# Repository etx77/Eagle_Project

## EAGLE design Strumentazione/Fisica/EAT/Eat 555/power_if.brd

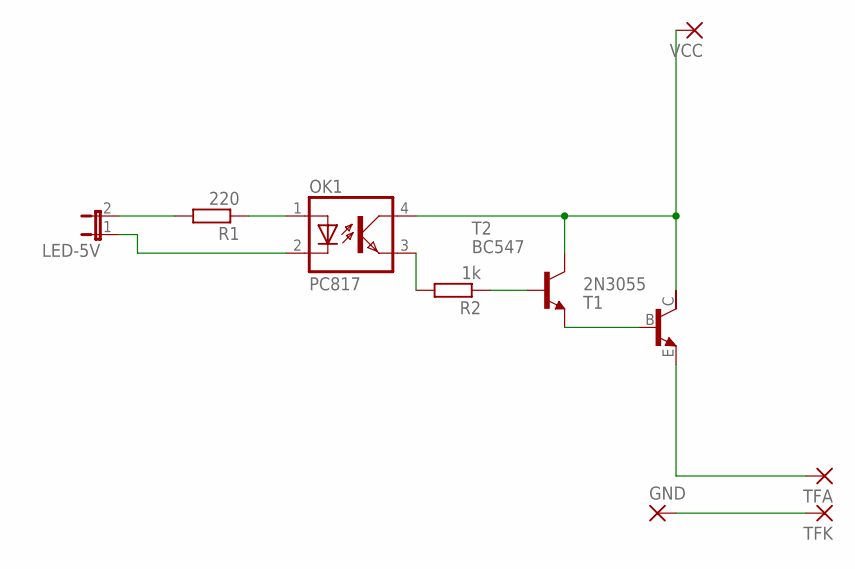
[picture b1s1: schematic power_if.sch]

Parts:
GND: 3,81/1,4
LED-5V: JP1E; JP1
OK1: PC817; DIL04
R1: 220; 0207/10
R2: 1k; 0207/10
T1: 2N3055; TO3
T2: BC547; TO92
TFA: 3,81/1,4
TFK: 3,81/1,4
VCC: 3,81/1,4

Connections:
unnamed: OK1.4 (COL), T1.C, T2.3 (C), VCC.1
unnamed: T1.B, T2.1 (E)
unnamed: OK1.3 (EMIT), R2.2
unnamed: R2.1, T2.2 (B)
unnamed: OK1.1 (A), R1.1
unnamed: LED-5V.2, R1.2
unnamed: LED-5V.1, OK1.2 (C)
unnamed: T1.E, TFA.1
unnamed: GND.1, TFK.1

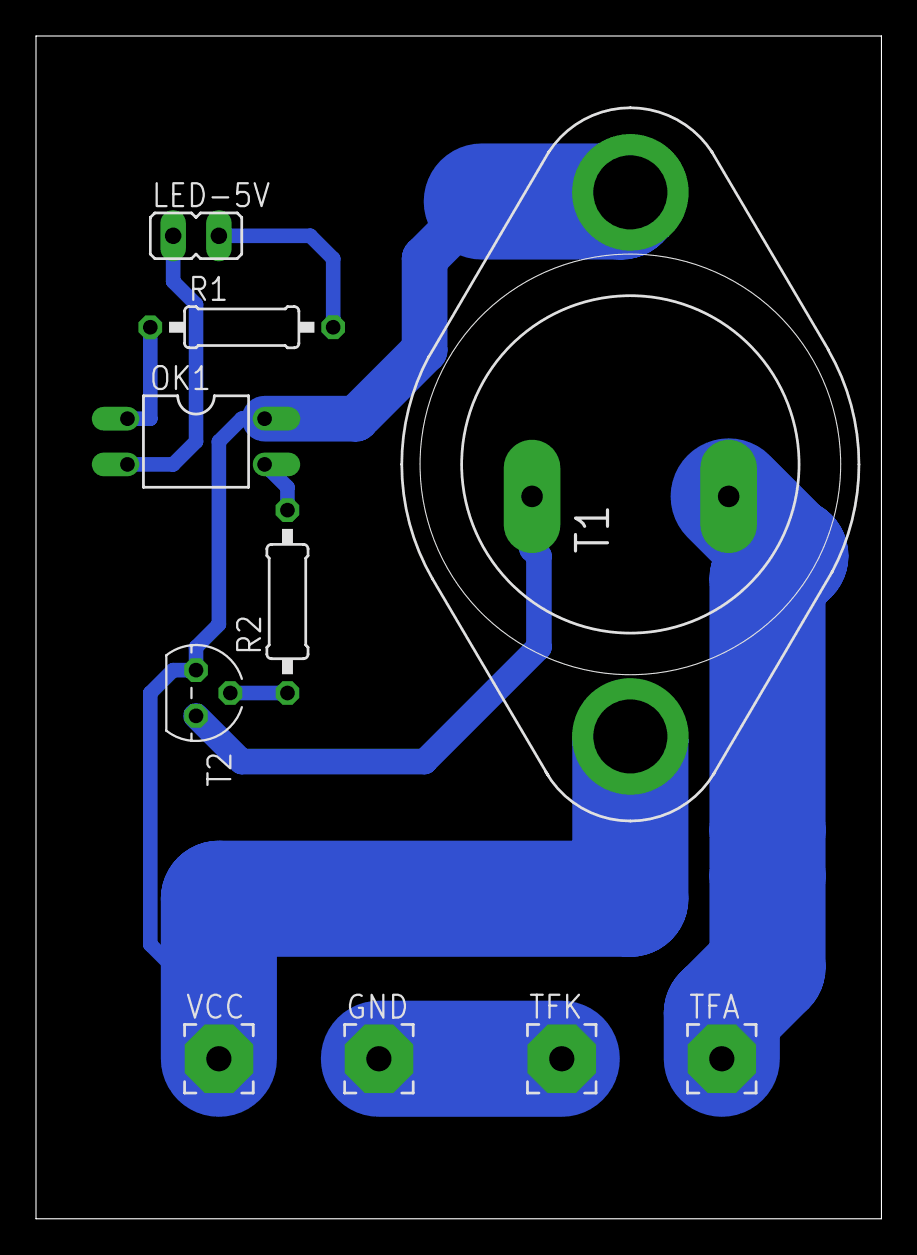
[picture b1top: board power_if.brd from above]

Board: 2 copper layers, 47.0 x 65.7 mm, 10 parts (0 on the bottom side), 9 nets.

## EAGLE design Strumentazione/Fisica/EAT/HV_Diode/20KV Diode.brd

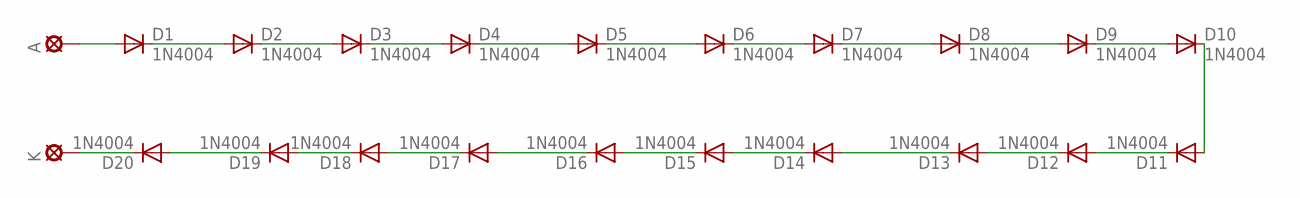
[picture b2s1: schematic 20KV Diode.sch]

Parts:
A: LSP10
D1, D2, D3, D4, D5, D6, D7, D8, D9, D10, D11, D12, D13, D14, D15, D16, D17, D18, D19, D20: 1N4004; DO41-10
K: LSP10

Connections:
unnamed: D9.C, D10.A
unnamed: D14.C, D15.A
unnamed: D15.C, D16.A
unnamed: D16.C, D17.A
unnamed: D17.C, D18.A
unnamed: D18.C, D19.A
unnamed: A.MP, D1.A
unnamed: D20.C, K.MP
unnamed: D1.C, D2.A
unnamed: D2.C, D3.A
unnamed: D3.C, D4.A
unnamed: D4.C, D5.A
unnamed: D5.C, D6.A
unnamed: D6.C, D7.A
unnamed: D7.C, D8.A
unnamed: D8.C, D9.A
unnamed: D10.C, D11.A
unnamed: D11.C, D12.A
unnamed: D12.C, D13.A
unnamed: D13.C, D14.A
unnamed: D19.C, D20.A

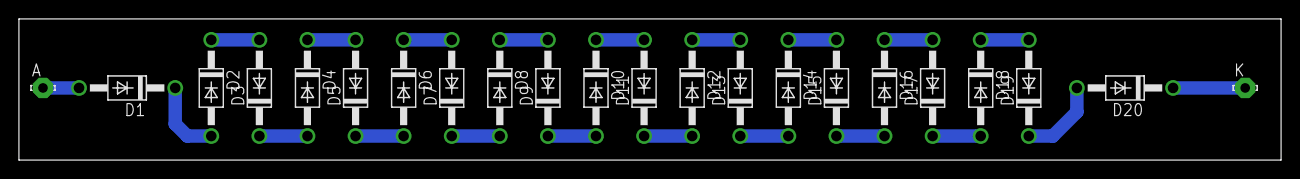
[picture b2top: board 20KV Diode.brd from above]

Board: 2 copper layers, 133.3 x 14.9 mm, 22 parts (0 on the bottom side), 21 nets.

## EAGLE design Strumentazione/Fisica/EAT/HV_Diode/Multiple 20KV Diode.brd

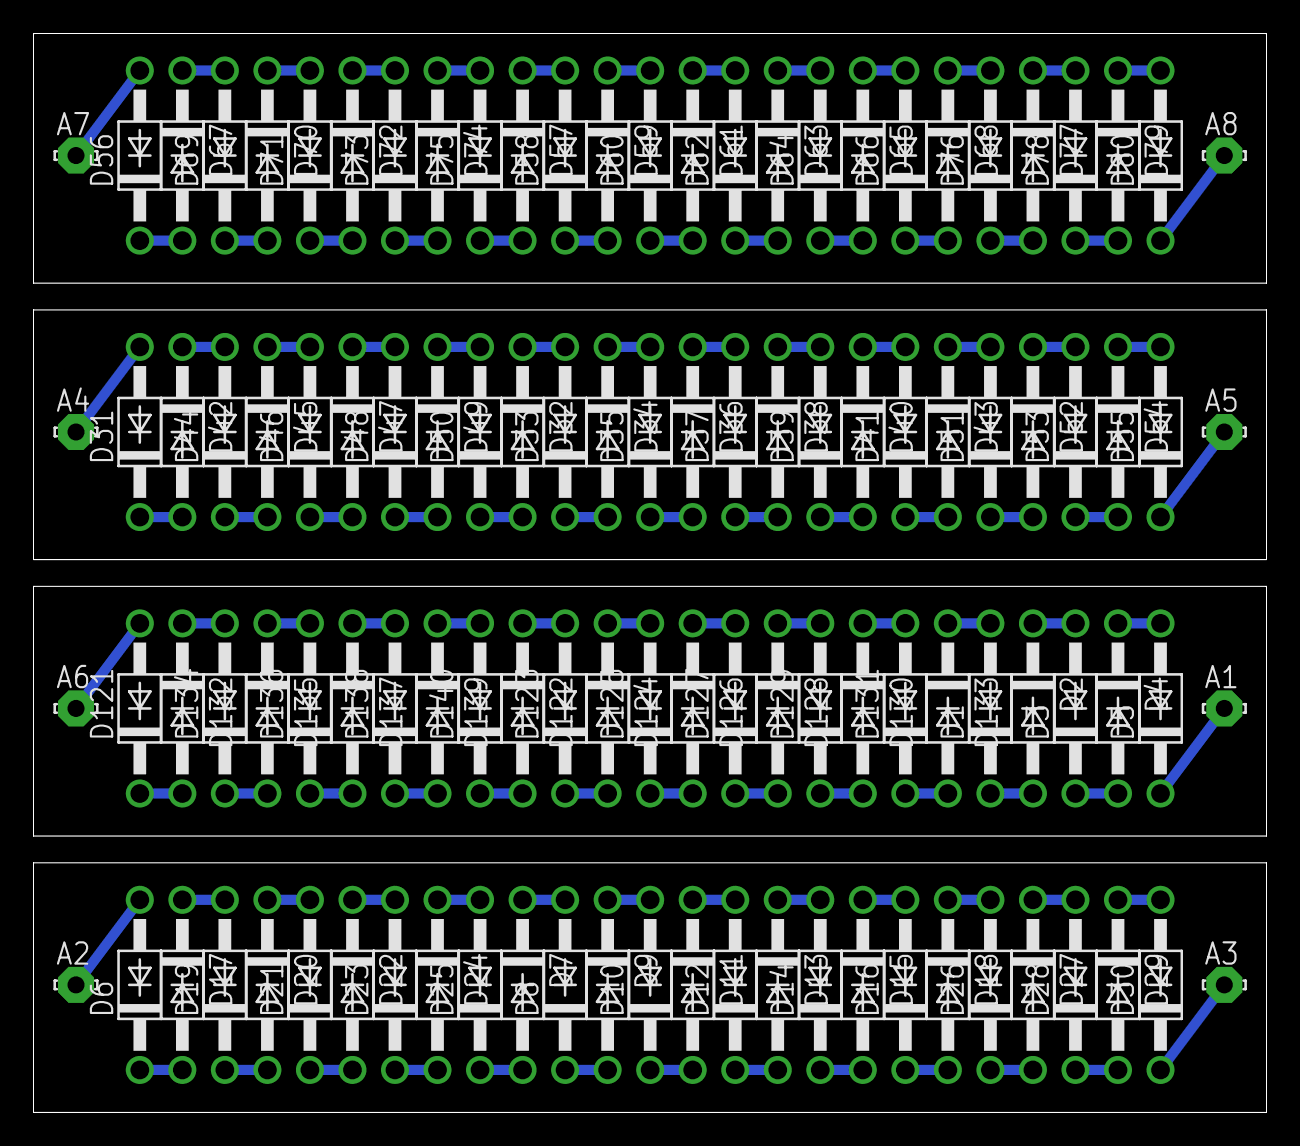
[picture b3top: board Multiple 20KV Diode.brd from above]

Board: 2 copper layers, 73.6 x 64.4 mm, 108 parts (0 on the bottom side), 104 nets.

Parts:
A1, A2, A3, A4, A5, A6, A7, A8: LSP10
D1, D2, D3, D4, D5, D6, D7, D8, D9, D10, D11, D12, D13, D14, D15, D16, D17, D18, D19, D20, D21, D22, D23, D24, D25, D26, D27, D28, D29, D30, D31, D32, D33, D34, D35, D36, D37, D38, D39, D40, D41, D42, D43, D44, D45, D46, D47, D48, D49, D50, D51, D52, D53, D54, D55, D56, D57, D58, D59, D60, D61, D62, D63, D64, D65, D66, D67, D68, D69, D70, D71, D72, D73, D74, D75, D76, D77, D78, D79, D80, D121, D122, D123, D124, D125, D126, D127, D128, D129, D130, D131, D132, D133, D134, D135, D136, D137, D138, D139, D140: 1N4004; DO41-10

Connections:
unnamed: D7.A, D25.C
unnamed: D11.C, D12.A
unnamed: D12.C, D13.A
unnamed: D13.C, D14.A
unnamed: D14.C, D15.A
unnamed: D15.C, D16.A
unnamed: A2.MP, D6.A
unnamed: D18.C, D26.A
unnamed: D6.C, D17.A
unnamed: D17.C, D19.A
unnamed: D19.C, D20.A
unnamed: D20.C, D21.A
unnamed: D21.C, D22.A
unnamed: D22.C, D23.A
unnamed: D23.C, D24.A
unnamed: D24.C, D25.A
unnamed: D7.C, D8.A
unnamed: D8.C, D9.A
unnamed: D9.C, D10.A
unnamed: D10.C, D11.A
unnamed: D16.C, D18.A
unnamed: D32.A, D50.C
unnamed: D36.C, D37.A
unnamed: D37.C, D38.A
unnamed: D38.C, D39.A
unnamed: D39.C, D40.A
unnamed: D40.C, D41.A
unnamed: A4.MP, D31.A
unnamed: D43.C, D51.A
unnamed: D31.C, D42.A
unnamed: D42.C, D44.A
unnamed: D44.C, D45.A
unnamed: D45.C, D46.A
unnamed: D46.C, D47.A
unnamed: D47.C, D48.A
unnamed: D48.C, D49.A
unnamed: D49.C, D50.A
unnamed: D32.C, D33.A
unnamed: D33.C, D34.A
unnamed: D34.C, D35.A
unnamed: D35.C, D36.A
unnamed: D41.C, D43.A
unnamed: D57.A, D75.C
unnamed: D61.C, D62.A
unnamed: D62.C, D63.A
unnamed: D63.C, D64.A
unnamed: D64.C, D65.A
unnamed: D65.C, D66.A
unnamed: A7.MP, D56.A
unnamed: D68.C, D76.A
unnamed: D56.C, D67.A
unnamed: D67.C, D69.A
unnamed: D69.C, D70.A
unnamed: D70.C, D71.A
unnamed: D71.C, D72.A
unnamed: D72.C, D73.A
unnamed: D73.C, D74.A
unnamed: D74.C, D75.A
unnamed: D57.C, D58.A
unnamed: D58.C, D59.A
unnamed: D59.C, D60.A
unnamed: D60.C, D61.A
unnamed: D66.C, D68.A
unnamed: D122.A, D140.C
unnamed: D126.C, D127.A
unnamed: D127.C, D128.A
unnamed: D128.C, D129.A
unnamed: D129.C, D130.A
unnamed: D130.C, D131.A
unnamed: A6.MP, D121.A
unnamed: D1.A, D133.C
unnamed: D121.C, D132.A
unnamed: D132.C, D134.A
unnamed: D134.C, D135.A
unnamed: D135.C, D136.A
unnamed: D136.C, D137.A
unnamed: D137.C, D138.A
unnamed: D138.C, D139.A
unnamed: D139.C, D140.A
unnamed: D122.C, D123.A
unnamed: D123.C, D124.A
unnamed: D124.C, D125.A
unnamed: D125.C, D126.A
unnamed: D131.C, D133.A
S$1: D1.C, D2.A
S$2: D2.C, D3.A
S$3: D3.C, D4.A
S$4: D4.C, D5.A
S$5: A1.MP, D5.C
S$6: D26.C, D27.A
S$7: D27.C, D28.A
S$8: D28.C, D29.A
S$9: D29.C, D30.A
S$10: A3.MP, D30.C
S$11: D51.C, D52.A
S$12: D52.C, D53.A
S$13: D53.C, D54.A
S$14: D54.C, D55.A
S$15: A5.MP, D55.C
S$16: D76.C, D77.A
S$17: D77.C, D78.A
S$18: D78.C, D79.A
S$19: D79.C, D80.A
S$20: A8.MP, D80.C

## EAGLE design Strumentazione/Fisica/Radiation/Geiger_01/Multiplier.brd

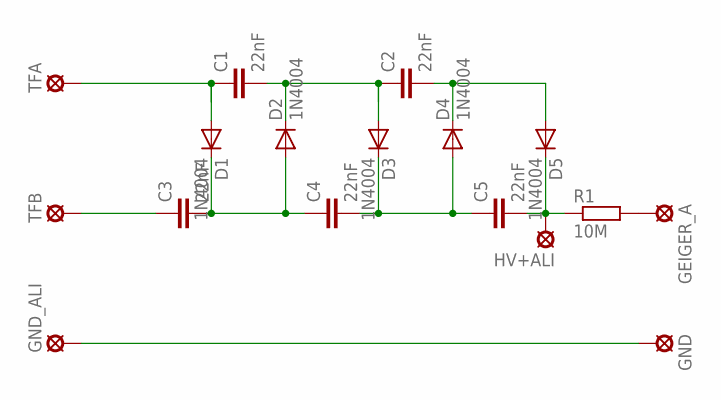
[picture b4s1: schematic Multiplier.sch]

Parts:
C1, C2, C3, C4, C5: 22nF; C025_050-025X075
D1, D2, D3, D4, D5: 1N4004; DO41-10
GEIGER_A: LSP10
GND: LSP10
GND_ALI: LSP10
HV+ALI: LSP10
R1: 10M; 0309/10
TFA: LSP10
TFB: LSP10

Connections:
unnamed: C3.2, C4.1, D1.C, D2.A
unnamed: C4.2, C5.1, D3.C, D4.A
unnamed: C5.2, D5.C, HV+ALI.MP, R1.1
unnamed: C2.2, D4.C, D5.A
unnamed: C1.2, C2.1, D2.C, D3.A
unnamed: C1.1, D1.A, TFA.MP
unnamed: C3.1, TFB.MP
unnamed: GEIGER_A.MP, R1.2
unnamed: GND.MP, GND_ALI.MP

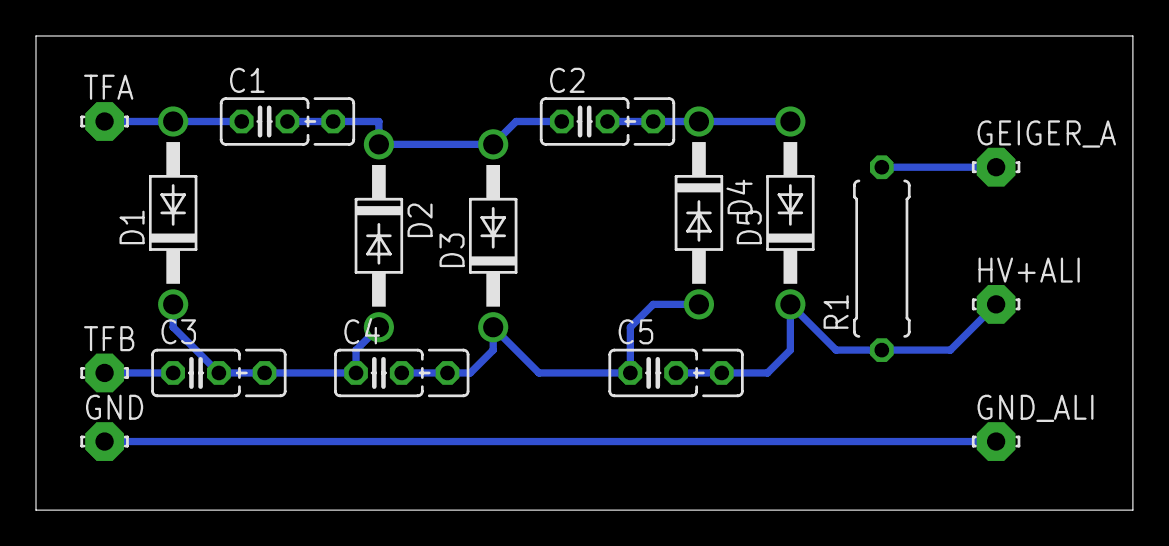
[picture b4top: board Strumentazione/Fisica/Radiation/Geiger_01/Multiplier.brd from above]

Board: 2 copper layers, 60.9 x 26.3 mm, 17 parts (0 on the bottom side), 9 nets.

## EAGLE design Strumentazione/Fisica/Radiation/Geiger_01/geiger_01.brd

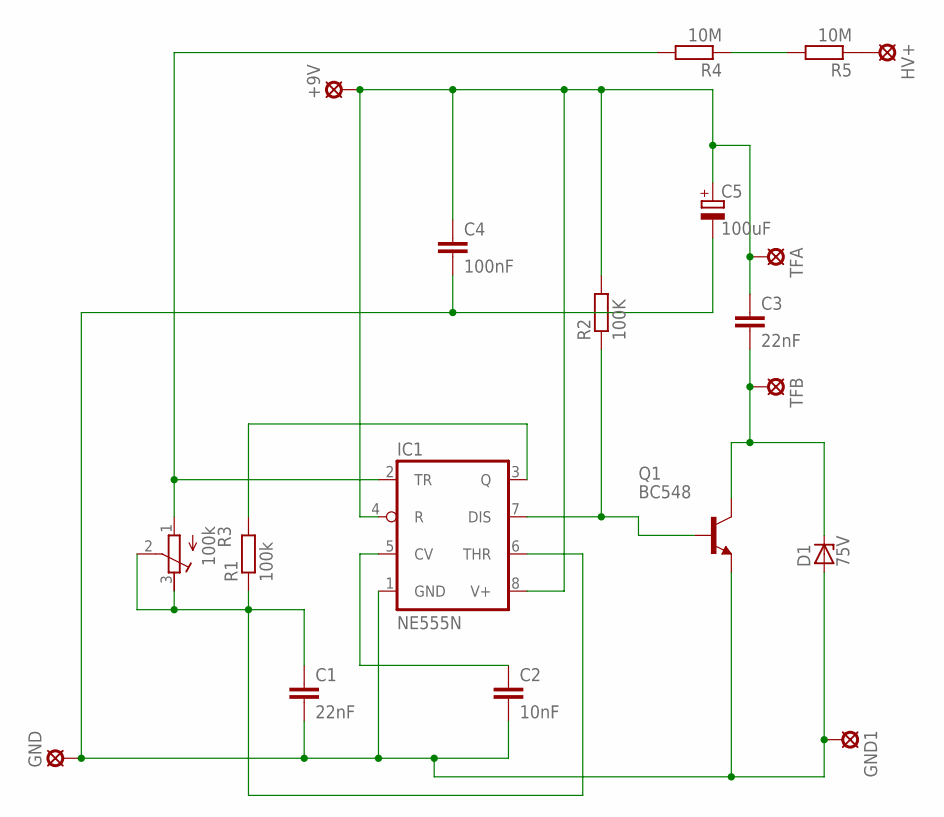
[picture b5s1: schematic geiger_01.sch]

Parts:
+9V: LSP10
C1, C3: 22nF; C050-024X044
C2: 10nF; C050-024X044
C4: 100nF; C050-024X044
C5: 100uF; E2,5-7
D1: 75V; P1Z12
GND, GND1: LSP10
HV+: LSP10
IC1: NE555N; DIL08
Q1: BC548; TO92-EBC
R1: 100k; 0207/12
R2: 100K; 0207/12
R3: 100k; RTRIM3339P
R4, R5: 10M; 0207/12
TFA: LSP10
TFB: LSP10

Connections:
unnamed: +9V.MP, C3.1, C4.1, C5.+, IC1.4 (R), IC1.8 (V+), R2.2, TFA.MP
unnamed: C1.1, IC1.6 (THR), R1.1, R3.2 (S), R3.3 (E)
unnamed: C2.1, IC1.5 (CV)
unnamed: IC1.7 (DIS), Q1.B, R2.1
unnamed: IC1.3 (Q), R1.2
unnamed: IC1.2 (TR), R3.1 (A), R4.2
unnamed: C1.2, C2.2, C4.2, C5.-, D1.A, GND.MP, GND1.MP, IC1.1 (GND), Q1.E
unnamed: R4.1, R5.2
unnamed: HV+.MP, R5.1
TFB: C3.2, D1.C, Q1.C, TFB.MP

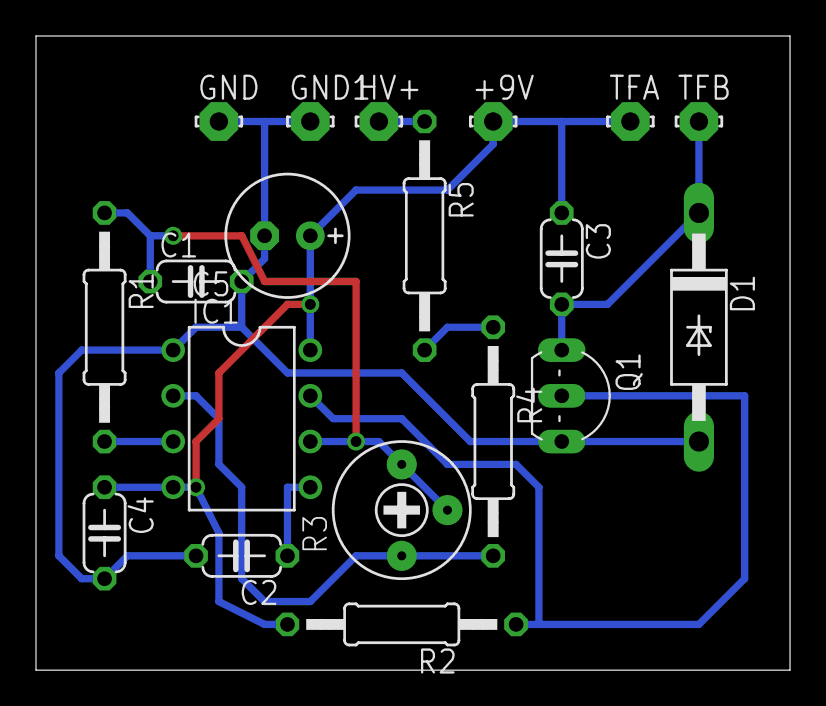
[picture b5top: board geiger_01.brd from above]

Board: 2 copper layers, 41.9 x 35.2 mm, 19 parts (0 on the bottom side), 10 nets.

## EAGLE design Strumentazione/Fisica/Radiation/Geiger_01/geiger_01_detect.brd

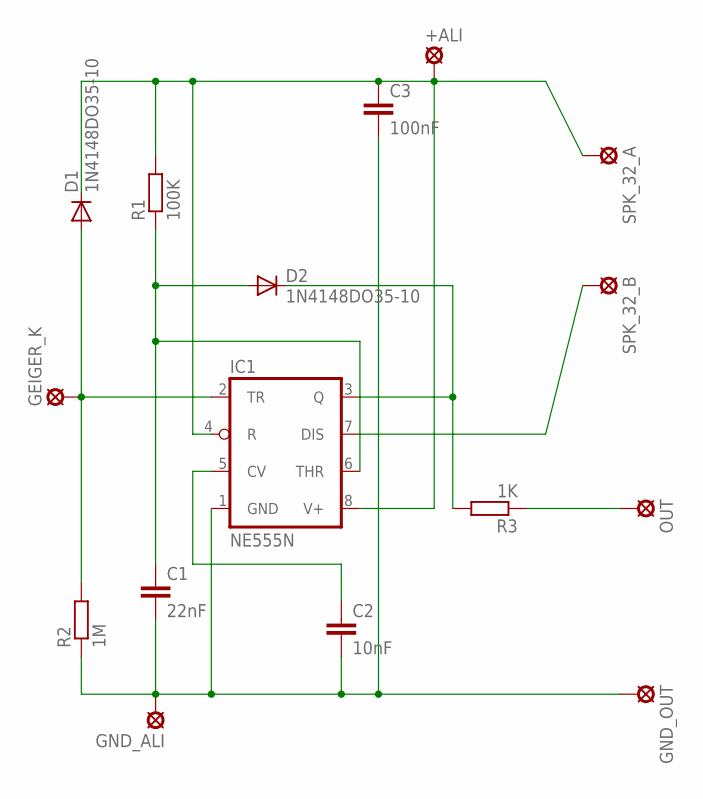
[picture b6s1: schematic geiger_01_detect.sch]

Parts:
+ALI: LSP10
C1: 22nF; C050-025X075
C2: 10nF; C050-025X075
C3: 100nF; C050-025X075
D1, D2: 1N4148DO35-10; DO35-10
GEIGER_K: LSP10
GND_ALI: LSP10
GND_OUT: LSP10
IC1: NE555N; DIL08
OUT: LSP10
R1: 100K; 0207/12
R2: 1M; 0207/12
R3: 1K; 0207/12
SPK_32_A, SPK_32_B: LSP10

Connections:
unnamed: OUT.MP, R3.1
unnamed: C1.1, D2.A, IC1.6 (THR), R1.1
unnamed: +ALI.MP, C3.1, D1.C, IC1.4 (R), IC1.8 (V+), R1.2, SPK_32_A.MP
unnamed: C2.1, IC1.5 (CV)
unnamed: C1.2, C2.2, C3.2, GND_ALI.MP, GND_OUT.MP, IC1.1 (GND), R2.1
unnamed: D2.C, IC1.3 (Q), R3.2
unnamed: D1.A, GEIGER_K.MP, IC1.2 (TR), R2.2
unnamed: IC1.7 (DIS), SPK_32_B.MP

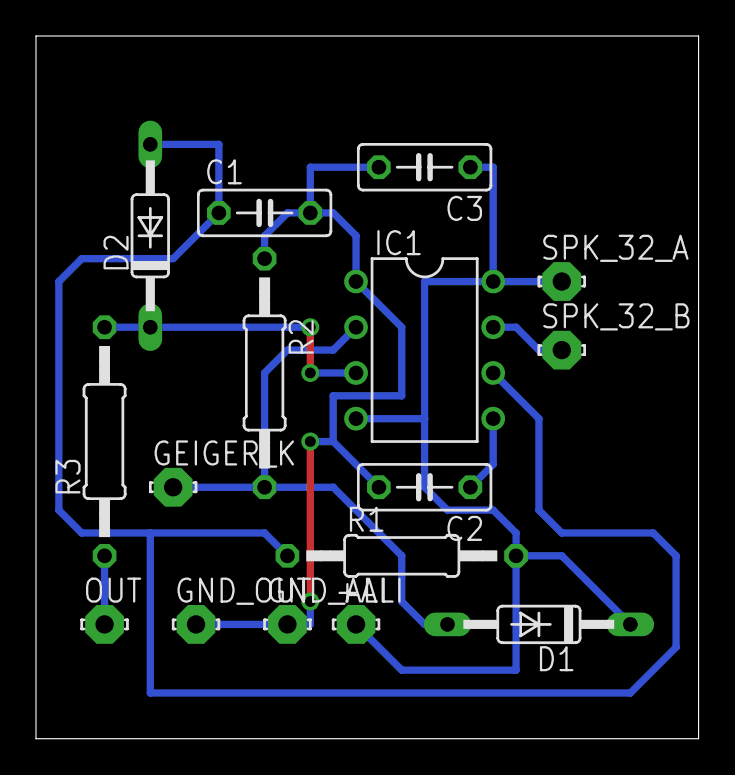
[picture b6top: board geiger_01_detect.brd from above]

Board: 2 copper layers, 36.8 x 39.0 mm, 16 parts (0 on the bottom side), 8 nets.

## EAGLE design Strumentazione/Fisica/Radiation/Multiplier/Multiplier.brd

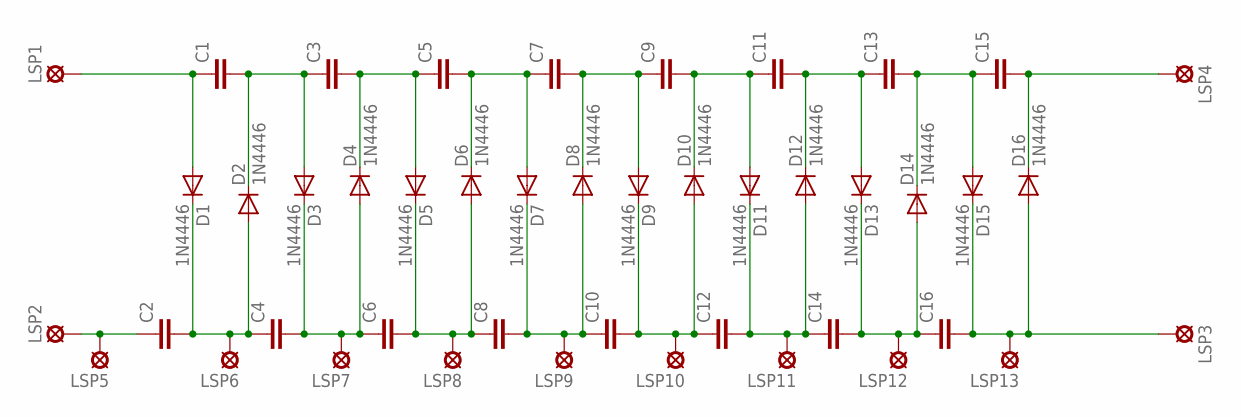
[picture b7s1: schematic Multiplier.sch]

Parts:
C1, C2, C3, C4, C5, C6, C7, C8, C9, C10, C11, C12, C13, C14, C15, C16: C5/4.5; C5B4.5
D1, D2, D3, D4, D5, D6, D7, D8, D9, D10, D11, D12, D13, D14, D15, D16: 1N4446; DO35-10
LSP1, LSP2, LSP3, LSP4, LSP5, LSP6, LSP7, LSP8, LSP9, LSP10, LSP11, LSP12, LSP13: LSP10

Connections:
unnamed: C1.1, D1.A, LSP1.MP
unnamed: C2.1, LSP2.MP, LSP5.MP
unnamed: C2.2, C4.1, D1.C, D2.A, LSP6.MP
unnamed: C4.2, C6.1, D3.C, D4.A, LSP7.MP
unnamed: C6.2, C8.1, D5.C, D6.A, LSP8.MP
unnamed: C8.2, C10.1, D7.C, D8.A, LSP9.MP
unnamed: C10.2, C12.1, D9.C, D10.A, LSP10.MP
unnamed: C12.2, C14.1, D11.C, D12.A, LSP11.MP
unnamed: C14.2, C16.1, D13.C, D14.A, LSP12.MP
unnamed: C16.2, D15.C, D16.A, LSP3.MP, LSP13.MP
unnamed: C1.2, C3.1, D2.C, D3.A
unnamed: C3.2, C5.1, D4.C, D5.A
unnamed: C5.2, C7.1, D6.C, D7.A
unnamed: C7.2, C9.1, D8.C, D9.A
unnamed: C9.2, C11.1, D10.C, D11.A
unnamed: C11.2, C13.1, D12.C, D13.A
unnamed: C13.2, C15.1, D14.C, D15.A
unnamed: C15.2, D16.C, LSP4.MP

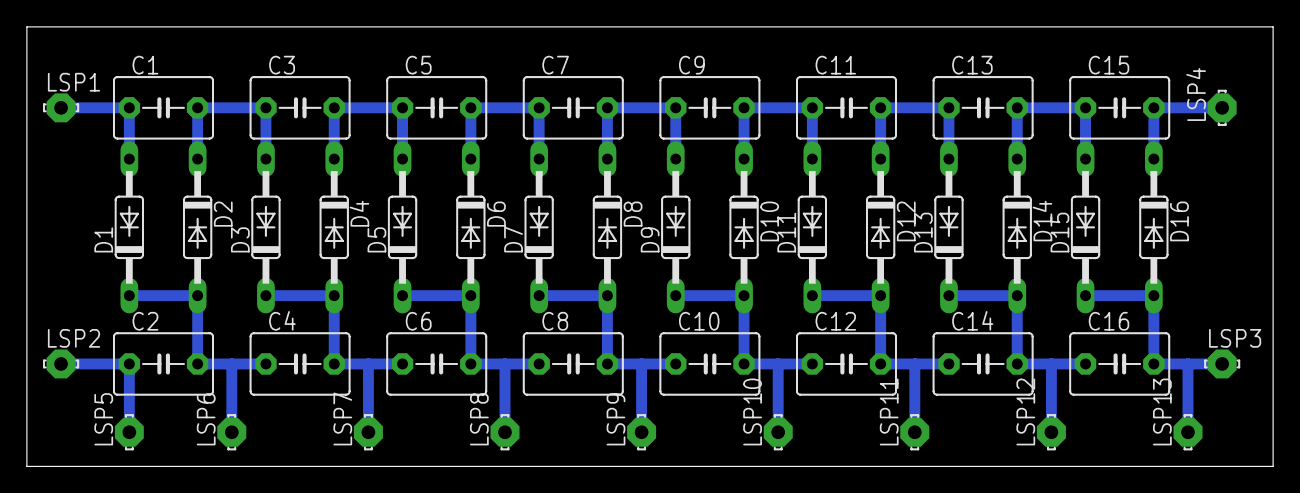
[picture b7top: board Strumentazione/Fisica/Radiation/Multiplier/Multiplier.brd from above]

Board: 2 copper layers, 92.7 x 32.7 mm, 45 parts (0 on the bottom side), 18 nets.
